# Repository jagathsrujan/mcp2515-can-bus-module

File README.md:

# MCP2515 CAN Bus Module — an agentic PCB design, end to end

A complete hardware design of an MCP2515-based CAN bus module, from the first requirements to a JLCPCB-ready manufacturing package. Nearly all of the engineering work was done by AI agents: **Claude Opus** as lead hardware engineer and reviewer, with **Claude Sonnet** subagents doing the research and the hands-on KiCad work. A human approved each phase before the next one started.

| | |
|---|---|
| **Board** | Rev A, 70 × 50 mm, 2-layer, 1.6 mm FR-4, 1 oz, all SMD on the top side |
| **Function** | Stand-alone CAN 2.0B controller (MCP2515) + ISO 11898-2 transceiver (TCAN1042), SPI to any 3.3 V or 5 V host |
| **Power** | 9 V DC input (7–16 V operating), protected, 5 V buck on board |
| **Design size** | 73 components, 43 nets, 4 schematic sheets |
| **Checks** | ERC 0 · DRC 0 · schematic/PCB parity 0 · 0 unconnected pads |
| **Status** | Phase 8 complete: validated for a prototype order. **Not yet fabricated or bench-tested.** |

---

## 1. What the board does

```
 9V ─J1─[PTC]─[SS34]─[TVS + 100µF]─[ferrite]─[AP63205 5V buck]─┬─ +5V ──► TCAN1042 VCC (bus side)
                                                                └─[3.3V LDO]·· SJ1 (open) ··┐
                                                                                            ▼
 Host ─J2─ VIO (3.0–5.5 V) ─────────────────────────────────────────┬──► MCP2515 VDD
        SCK, MOSI, CS, RST ──► MCP2515 ◄── 16 MHz crystal           └──► TCAN1042 VIO
        MISO, INT ◄─────────── MCP2515
                                 │TXCAN ▲RXCAN
                                 ▼      │
                         TCAN1042 ──[CMC footprint, DNP]──[split 120 Ω, JP1]──[CAN TVS]── J3 / J4
```

The main architecture decision (D-001) is a **host-referenced logic domain**. The MCP2515 and the transceiver's logic pins both run from the host's own `VIO` pin, so the board works with a 3.3 V ESP32/STM32 or a 5 V Arduino without level shifters and without a jumper that could put 5 V into a 3.3 V host. The transceiver's bus side runs from an on-board 5 V rail, so the CAN levels are full ISO 11898-2 whatever the host voltage.

Other features:
- Reverse-polarity, overcurrent (PTC) and transient (TVS) protection on the 9 V input
- ±20 kV ESD protection on CAN_H / CAN_L (PESD2CANFD27V), placed at the connectors
- Split 2 × 60 Ω termination with a 4.7 nF centre tap, both legs switched by jumper JP1
- Two CAN terminals for daisy-chaining, an optional common-mode choke footprint, an optional 3.3 V LDO for testing without a host
- Exact bit timing at 125 k / 250 k / 500 k / 1 Mbit/s from the 16 MHz crystal
- 12 labelled test points, 3 fiducials, 2 × M3 mounting holes

## 2. How the agents worked

### Roles

| Role | Model | Did |
|---|---|---|
| Human | — | Wrote the brief, answered open questions, **approved every phase** before the next started, made sourcing calls (e.g. the MCP2515 part number change) |
| Lead engineer / reviewer | Claude Opus | Requirements, architecture, every design decision and calculation, plans for each phase, and **independent verification** of everything the builders produced |
| Researchers / builders | Claude Sonnet subagents | Datasheet extraction, JLCPCB capability research, schematic capture and PCB layout in KiCad through the KiCad MCP server, manufacturing exports, stock checks |

### Rules that kept it honest

1. **One source of truth.** [`docs/ENGINEERING_SPEC.md`](docs/ENGINEERING_SPEC.md) holds every requirement (R-xx), decision (D-001…D-032), open question (Q-xx) and a change log. Every session read it first, and Sonnet was not allowed to override a decision marked APPROVED.
2. **Phase gates.** Eight phases, each ending with a written report and a human approval. No phase started before the previous one was approved.
3. **Every number is tagged.** `[DS]` datasheet-verified with document and section, `[DS-pending]` quoted from memory and still to be checked, `[CALC]` calculated, `[ASSUME]` assumption, `[TEST]` needs a bench check. Values from memory were not used for final choices until a datasheet confirmed them.
4. **Plan → build → independent review.** Opus wrote the plan, Sonnet built it, then Opus re-checked with its own tools instead of trusting the builder's report: it re-ran ERC/DRC itself, parsed a fresh netlist export with its own parser, compared symbol pin maps with the datasheets, measured distances in the PCB with a pcbnew script, and opened every render.
5. **Margins over minimums.** JLCPCB rules were researched first and every project rule sits above JLC's limits (e.g. 0.15 mm track/space vs 0.10, 0.3 mm vias vs 0.15).

### The eight phases

| Phase | What happened | Output |
|---|---|---|
| 1. Requirements & architecture | Brief turned into requirements; derived requirements proposed (7–16 V input, VIO 3.0–5.5 V, ≤ 100 × 100 mm); block diagram, voltage domains, current budget; JLCPCB capabilities researched and copper-pour strategy set | [Spec §1–§6](docs/ENGINEERING_SPEC.md), [`jlcpcb_capabilities.md`](docs/research/jlcpcb_capabilities.md) |
| 2. Component selection | Candidates scored per function against datasheets, JLC stock and Basic/Extended class. Found that the planned P-MOSFET reverse-polarity stage would be overstressed at the TVS clamp voltage → switched to an SS34 Schottky (D-006r) | [`phase2_component_selection.md`](docs/phase2_component_selection.md), [`research/`](docs/research/) |
| 3. Power supply | LDO vs buck trade: LDOs fail thermally at 16 V / 85 °C → AP63205 buck. Full input protection chain and abs-max check at the 29.2 V clamp | [`phase3_power_supply.md`](docs/phase3_power_supply.md), [`power_budget.xlsx`](docs/power_budget.xlsx) |
| 4. MCP2515 & oscillator | 16 MHz crystal, load caps, drive level, bit-timing register values, reset and SPI conditioning | [`phase4_mcp2515_oscillator.md`](docs/phase4_mcp2515_oscillator.md) |
| 5. CAN physical layer | Transceiver mode pins, termination, TVS, choke option, bus-length limits | [`phase5_can_phy.md`](docs/phase5_can_phy.md) |
| 6. Schematic | Sonnet captured a hierarchical KiCad schematic (Power / Controller / CAN PHY). Opus review: ERC 0, every net checked, one annotation fix (J1B → J5) | [Schematic PDF](docs/schematic/MCP2515_CAN_schematic.pdf), [`phase6_schematic_review.md`](docs/phase6_schematic_review.md) |
| 7. PCB layout | Sonnet placed and routed with its own scripts (placement legaliser, grid A* router, zone/stitching/silk scripts; CAN pair by hand coordinates). Opus review found issues, one correction round fixed them, DRC 0 | [`phase7_pcb_review.md`](docs/phase7_pcb_review.md), [`pcb/layout_report.md`](docs/pcb/layout_report.md) |
| 8. Validation & manufacturing | Gerbers, drill, JLC BOM and CPL, stock check, requirement traceability, risk register, bring-up guide | [`final_design_validation.md`](docs/final/final_design_validation.md), [`manufacturing/`](docs/manufacturing/) |

### What the reviews caught

These are real issues caught by the review step before they reached a board:

- **P-MOSFET overstress (Phase 2):** gate–source and drain–source ratings would be exceeded when the input TVS clamps at 29.2 V, so the reverse-polarity stage was changed to a Schottky diode.
- **Transceiver standby default (Phase 2):** the TCAN1042 STB pin defaults to standby when left open, so a 10 kΩ pull-down was added. Without it the bus would stay silent.
- **No internal reset pull-up (Phase 2):** the MCP2515 has none, so an external 10 kΩ + 10 nF RC was added.
- **INT pin type (Phase 2):** it had been assumed open-drain; the datasheet shows push-pull, so a "don't share INT between modules" warning was documented.
- **ESD diode too far from the connectors (Phase 7):** the first layout put D3 12–18 mm away, with the bus able to branch before it. It was moved between J3/J4 so it is the first thing on the bus.
- **Terminal block drill too small (Phase 7):** the stock footprint had a 1.3 mm drill for a pin that needs 1.4 mm. A project footprint was made with 1.4 mm drill / 2.6 mm pad.
- **Courtyard too close to the edge (Phase 7):** D2 was 2.25 mm from the board edge against a 2.5 mm rule, so it was moved (now ≥ 2.7 mm).
- **Ambiguous "+ centre" silkscreen (Phase 7):** fixed.
- **End-of-life part (Phase 8):** JLC listed the MCP2515 part C12368 as no longer manufactured. It was switched to C153782 (MCP2515T-I/SO, same chip on tape and reel), and ERC/DRC were re-run.

### Tools

- **KiCad 10.0.8**, driven by Sonnet through a KiCad MCP server, plus `kicad-cli` for ERC, DRC, netlist, Gerber, drill, PDF and STEP exports
- Python scripts (pcbnew and s-expression parsing) for placement, routing, measurement and independent netlist checks
- Datasheets from the manufacturers and LCSC, and JLCPCB's own capability pages and KiCad export guide, all cited by URL in the research files
- Claude Code (desktop app) as the agent harness

## 3. Key design numbers

| Item | Value |
|---|---|
| +5V worst-case load | 114 mA (incl. 100 mA bus-short current) vs 150 mA design, buck rated 2 A |
| Hottest part | ≈ 45 mW (buck), so no thermal design needed |
| Input abs-max check | Everything survives the 29.2 V TVS clamp (SS34 40 V, C1 35 V, buck 35 V) |
| Reverse input | 16 V reverse blocked by D1 (40 V rating) |
| Bit timing (CNF1/2/3) | 1M 0x00/0x83/0x01 · 500k 0x00/0xAE/0x01 · 250k 0x01/0xAE/0x01 · 125k 0x03/0xAE/0x01 |
| Max bus length | ≈ 10–15 m at 1 Mbit/s, 52 m at 500k, 140 m at 250k, 315 m at 125k |
| Layout | Crystal 28 mm from the buck inductor; buck hot loop ≈ 4 mm²; decoupling ≤ 2 mm from pins; solid bottom ground; 126+ stitching vias; CAN pair length-matched |
| JLC rules | Track/space 0.15/0.15 mm min, vias 0.3/0.6 mm, copper 0.5 mm from edge, silk ≥ 1 mm |
| Component cost | ≈ $8.50 per board (Sonnet estimate, excl. PCB, assembly and Extended-part fees) |

## 4. Repository map

| What | Where |
|---|---|
| Spec, decisions and change log | [`docs/ENGINEERING_SPEC.md`](docs/ENGINEERING_SPEC.md) |
| Phase reports | `docs/phase2…phase7_*.md`, block netlists `docs/*_netlist.md` |
| Datasheet extracts & JLC research | [`docs/research/`](docs/research/) |
| KiCad project | [`kicad/MCP2515_CAN/`](kicad/MCP2515_CAN/) (with custom footprints in `MCP2515_CAN.pretty/`) |
| Schematic | [PDF](docs/schematic/MCP2515_CAN_schematic.pdf), sheet PNGs, netlist, BOM, ERC report in [`docs/schematic/`](docs/schematic/) |
| PCB | renders, layer images, DRC report, [3D STEP](docs/pcb/MCP2515_CAN.step) in [`docs/pcb/`](docs/pcb/) |
| Manufacturing (JLCPCB) | [Gerber zip](docs/manufacturing/MCP2515_CAN_RevA_gerbers.zip), BOM, CPL, rotation review, stock check in [`docs/manufacturing/`](docs/manufacturing/) |
| Final docs | [validation](docs/final/final_design_validation.md), [BOM](docs/final/BOM_final.csv), [connector pinouts](docs/final/connector_pinouts.md), [design notes](docs/final/design_notes.md), [testing & commissioning](docs/final/testing_commissioning.md) |

| Top copper + silk | Bottom copper |
|---|---|
|  |  |

## 5. What's still open

The design is validated on paper, not on a bench. The full risk register (K-01…K-17) is in [`final_design_validation.md` §9](docs/final/final_design_validation.md). The main items:

- **Before paying for the order:** check every part's rotation and polarity in JLC's placement preview, especially D1, D2, LED D4 and crystal Y1, which had no rotation-database rule. A reversed D2 would short the input. Also re-check stock and Extended-part fees.
- **On the first boards:** measure crystal drive level at 5 V VIO (calculated 227 µW vs 200 µW max; fit R4 ≈ 1 kΩ if needed), crystal frequency via CLKOUT, and +5V ripple at idle and under 1 Mbit/s traffic. Also check the fit of the three footprints made from datasheet drawings (barrel jack, terminal blocks, choke).
- **Not tested:** EMC emissions and IEC 61000-4-2 ESD.
- **Usage limits:** 7–16 V supplies only, centre-positive jack; ≤ 10 m bus at 1 Mbit/s; not for 24 V vehicle buses (the 27 V TVS standoff would conduct at charge voltage); one INT line per module.

The bring-up order and expected readings are in [`testing_commissioning.md`](docs/final/testing_commissioning.md).

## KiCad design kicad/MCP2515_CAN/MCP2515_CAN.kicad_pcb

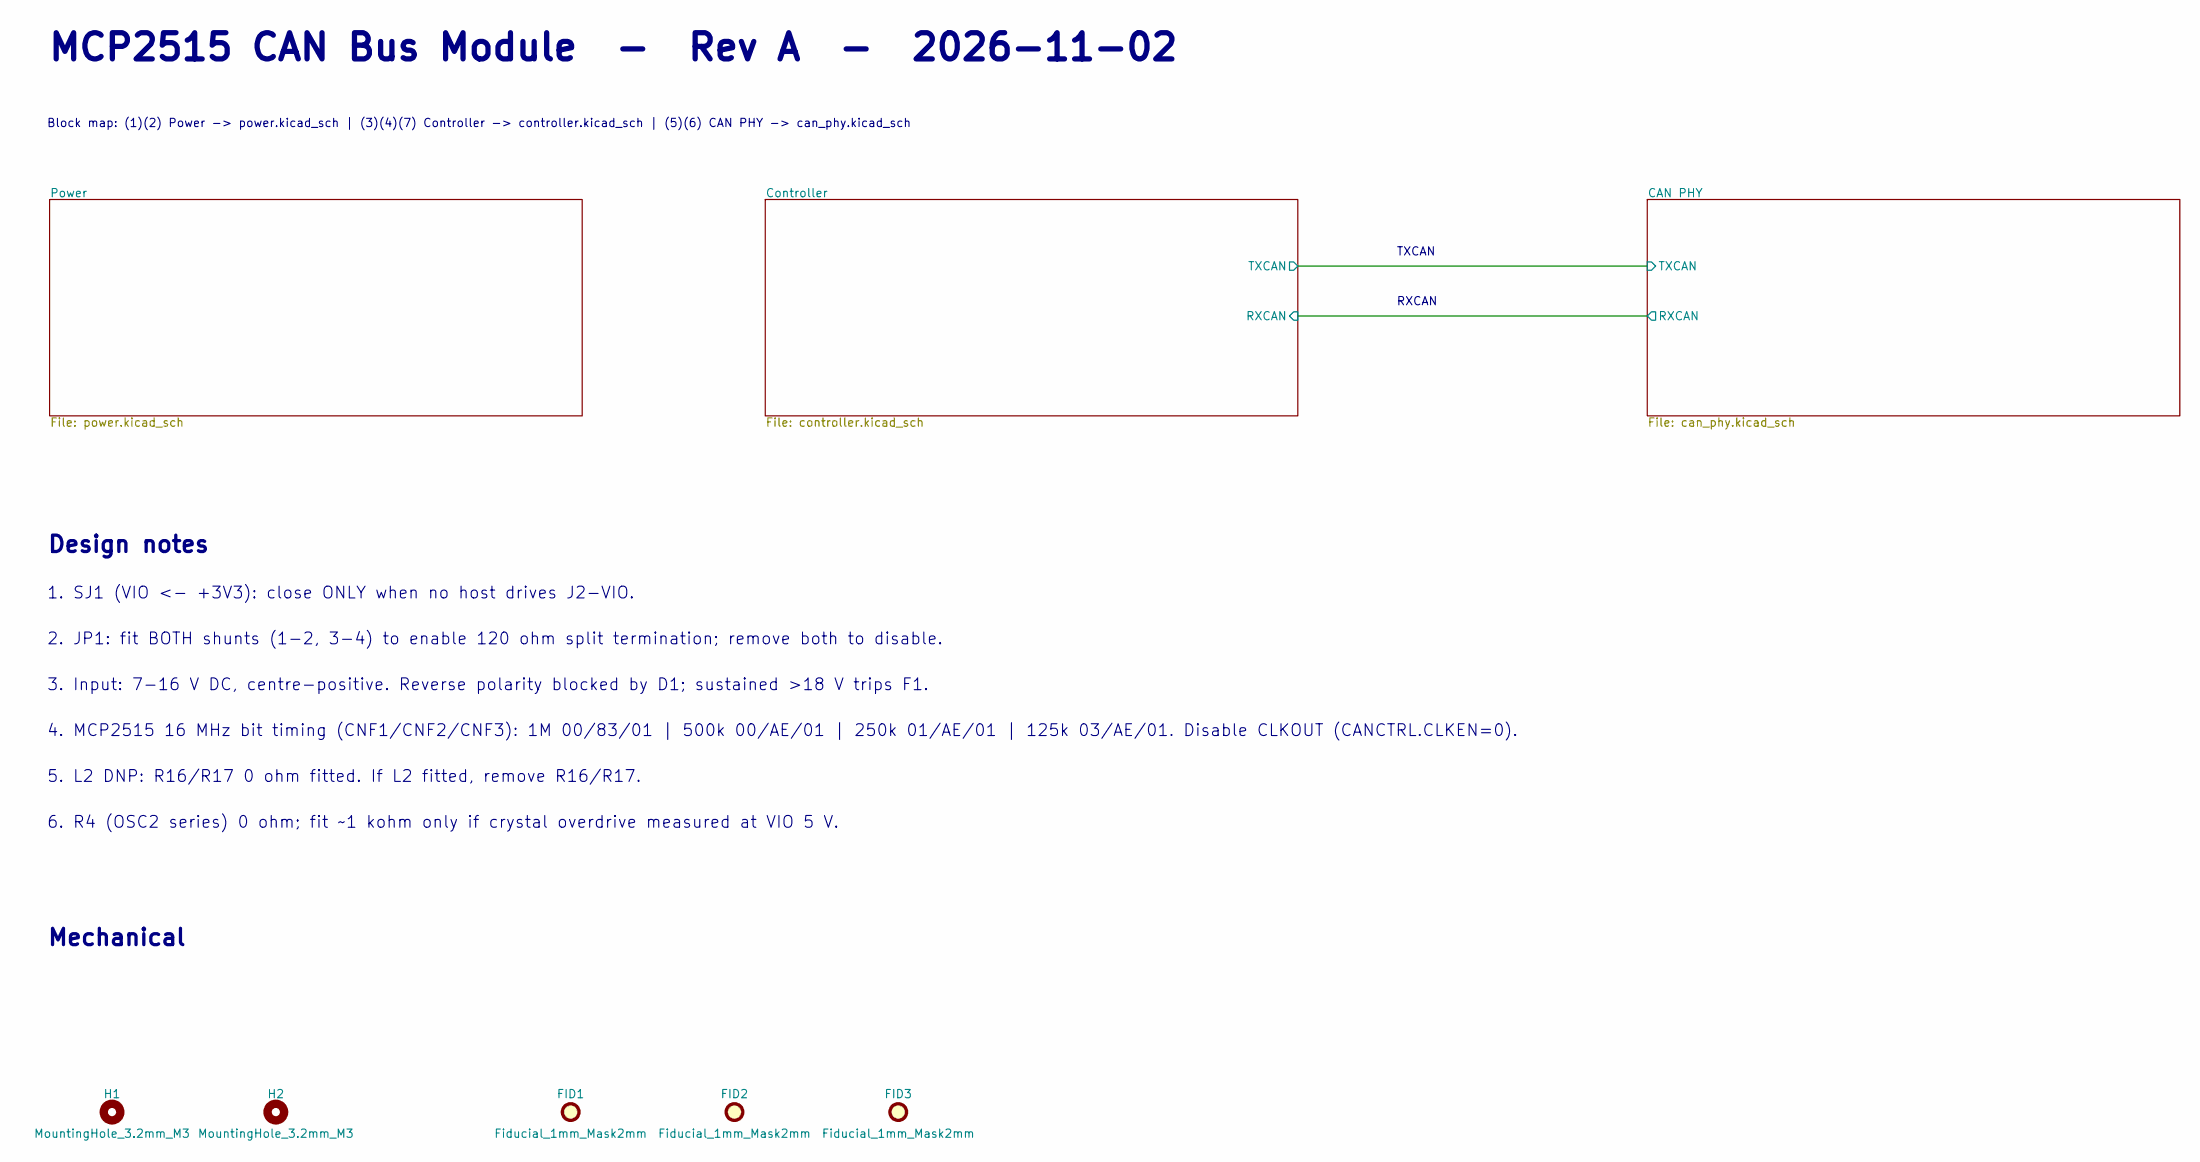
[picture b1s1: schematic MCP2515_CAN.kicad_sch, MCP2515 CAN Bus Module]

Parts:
FID1, FID2, FID3: Fiducial_1mm_Mask2mm
H1, H2: MountingHole_3.2mm_M3

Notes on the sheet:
TXCAN
RXCAN
MCP2515 CAN Bus Module - Rev A - 2026-11-02
Block map: (1)(2) Power -> power.kicad_sch | (3)(4)(7) Controller -> controller.kicad_sch | (5)(6) CAN PHY -> can_phy.kicad_sch
Design notes
1. SJ1 (VIO <- +3V3): close ONLY when no host drives J2-VIO.
2. JP1: fit BOTH shunts (1-2, 3-4) to enable 120 ohm split termination; remove both to disable.
3. Input: 7-16 V DC, centre-positive. Reverse polarity blocked by D1; sustained >18 V trips F1.
4. MCP2515 16 MHz bit timing (CNF1/CNF2/CNF3): 1M 00/83/01 | 500k 00/AE/01 | 250k 01/AE/01 | 125k 03/AE/01. Disable CLKOUT (CANCTRL.CLKEN=0).
5. L2 DNP: R16/R17 0 ohm fitted. If L2 fitted, remove R16/R17.
6. R4 (OSC2 series) 0 ohm; fit ~1 kohm only if crystal overdrive measured at VIO 5 V.
Mechanical

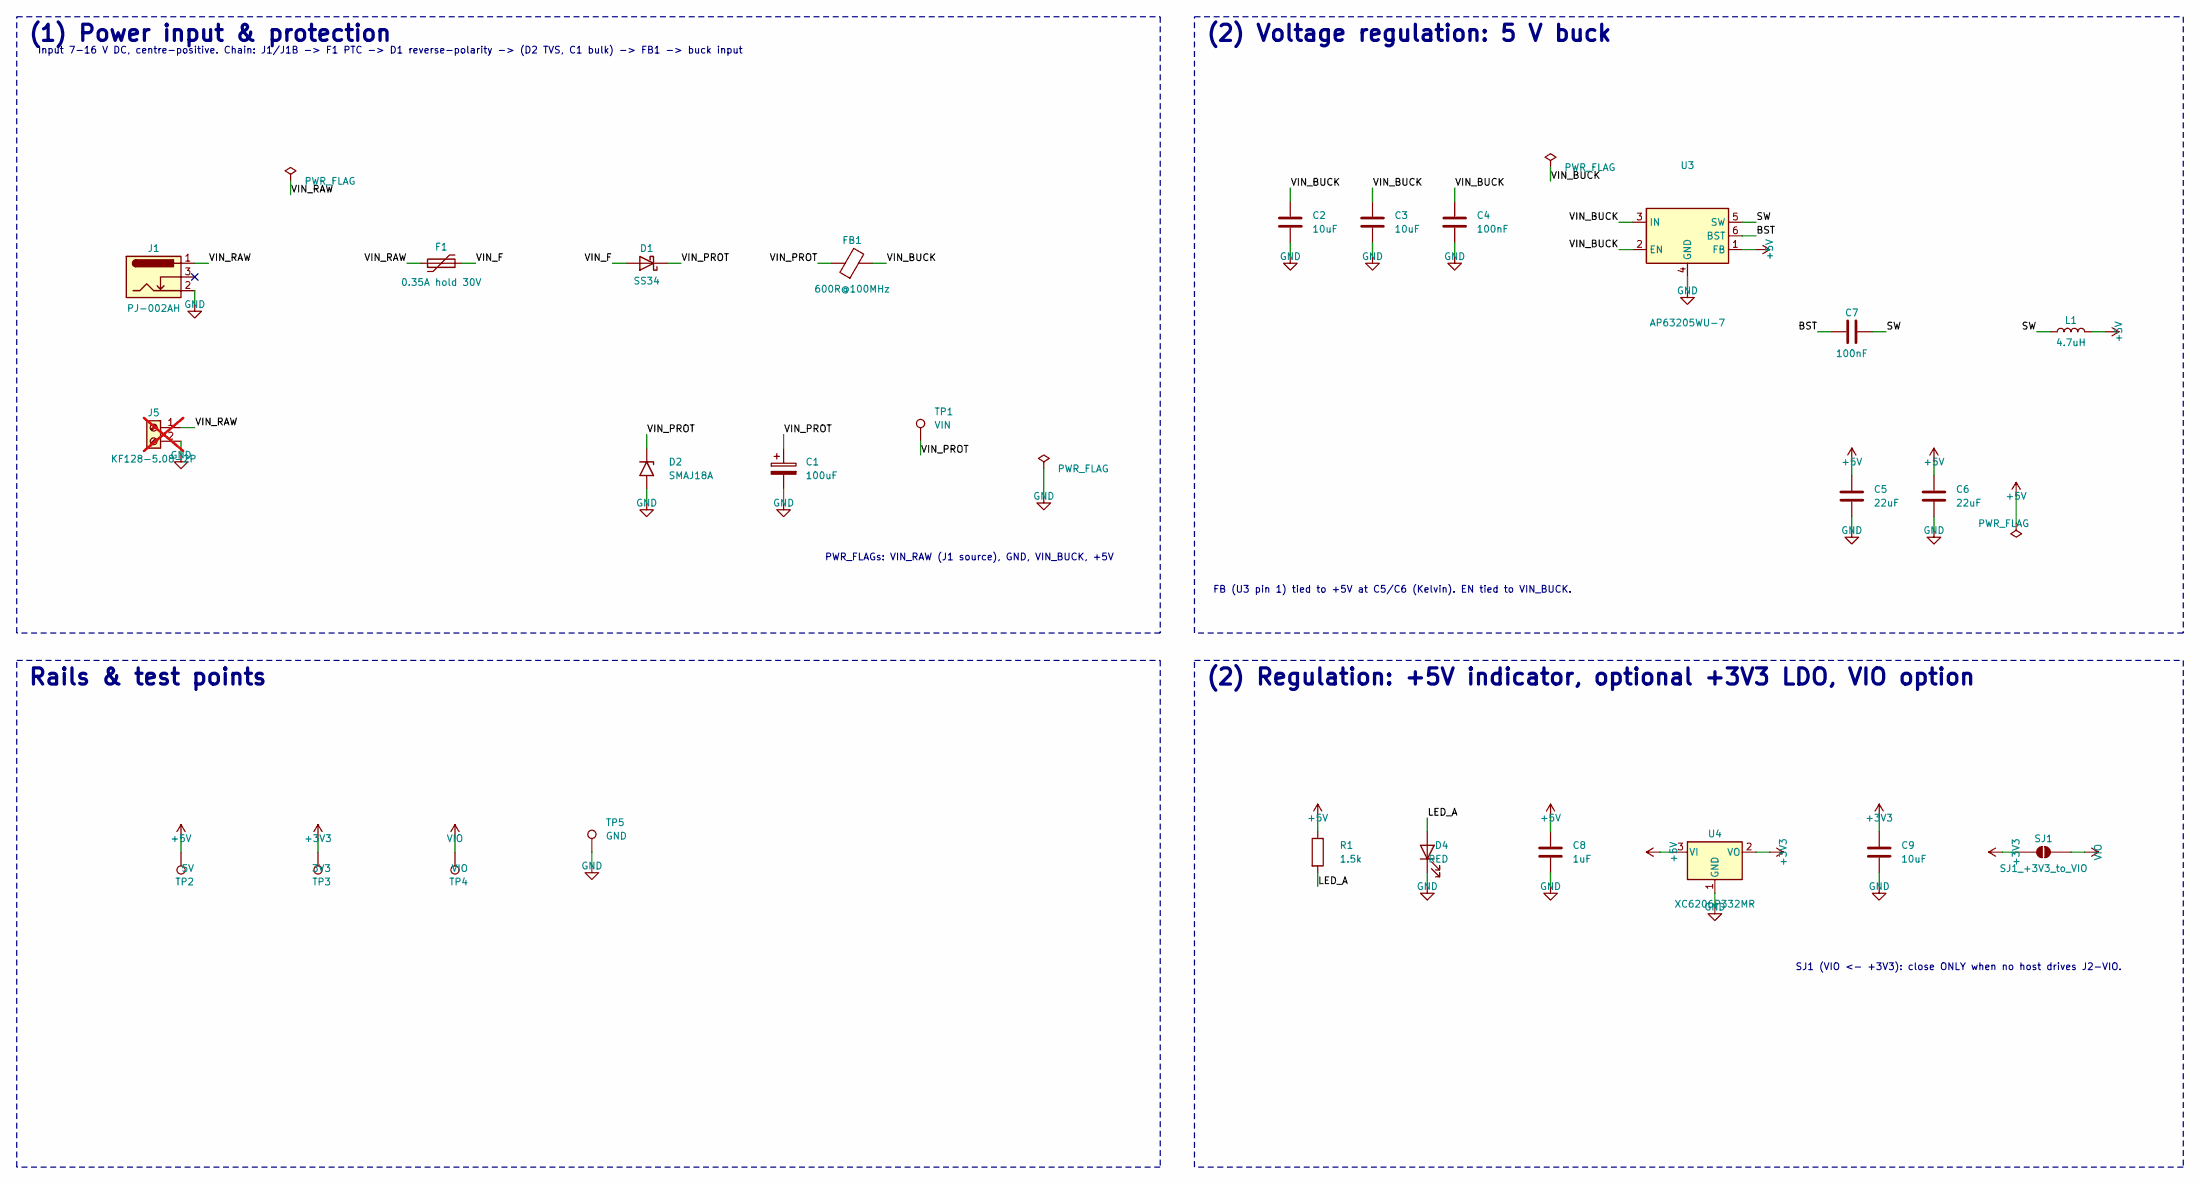
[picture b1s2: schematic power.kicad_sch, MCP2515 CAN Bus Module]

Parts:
C1: 100uF; CP_Elec_6.3x7.7; MPN FZ100UF35V90RV0064; LCSC C2992596
C2, C3: 10uF; C_1206_3216Metric; MPN CL31A106KBHNNNE; LCSC C13585
C4, C7: 100nF; C_0603_1608Metric; MPN CC0603KRX7R9BB104; LCSC C14663
C5, C6: 22uF; C_1206_3216Metric; MPN CL31A226KAHNNNE; LCSC C12891
C8: 1uF; C_0603_1608Metric; MPN CL10A105KB8NNNC; LCSC C15849
C9: 10uF; C_0805_2012Metric; MPN CL21A106KAYNNNE; LCSC C15850
D1: SS34; D_SMA; MPN SS34; LCSC C8678
D2: SMAJ18A; D_SMA; MPN SMAJ18A; LCSC C148219
D4: RED; LED_0603_1608Metric; MPN KT-0603R; LCSC C2286
F1: 0.35A hold 30V; Fuse_1206_3216Metric; MPN 0ZCJ0035AF2E; LCSC C6378052
FB1: 600R@100MHz; L_0805_2012Metric; MPN GZ2012D601TF; LCSC C1017
J1: PJ-002AH; BarrelJack_CUI_PJ-002AH; MPN PJ-002AH; LCSC C2961147
J5: KF128-5.08-2P; KF128-5.08-2P_Horizontal; MPN KF128-5.08-2P; LCSC C474952; not fitted
L1: 4.7uH; L_Sunlord_SWPA4020S; MPN SWPA4020S4R7MT; LCSC C48427
R1: 1.5k; R_0603_1608Metric; MPN 0603WAF1501T5E; LCSC C22843
SJ1: SJ1_+3V3_to_VIO; SolderJumper-2_P1.3mm_Open_RoundedPad1.0x1.5mm
TP1: VIN; TestPoint_Pad_D1.5mm
TP2: 5V; TestPoint_Pad_D1.5mm
TP3: 3V3; TestPoint_Pad_D1.5mm
TP4: VIO; TestPoint_Pad_D1.5mm
TP5: GND; TestPoint_Pad_D1.5mm
U3: AP63205WU-7; TSOT-23-6; MPN AP63205WU-7; LCSC C2071056
U4: XC6206P332MR; SOT-23-3; MPN XC6206P332MR; LCSC C5446

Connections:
+3V3: C9.1, SJ1.1 (A), TP3.1, U4.2 (VO)
+5V: C5.1, C6.1, C8.1, L1.2, R1.1, TP2.1, U3.1 (FB), U4.3 (VI); also elsewhere on the board
/Power/BST: C7.1, U3.6 (BST)
/Power/LED_A: D4.2 (A), R1.2
/Power/SW: C7.2, L1.1, U3.5 (SW)
/Power/VIN_BUCK: C2.1, C3.1, C4.1, FB1.2, U3.2 (EN), U3.3 (IN)
/Power/VIN_F: D1.2 (A), F1.2
/Power/VIN_PROT: C1.1, D1.1 (K), D2.1 (A1), FB1.1, TP1.1
/Power/VIN_RAW: F1.1, J1.1, J5.1
GND: C1.2, C2.2, C3.2, C4.2, C5.2, C6.2, C8.2, C9.2, D2.2 (A2), D4.1 (K), J1.2, J5.2, TP5.1, U3.4 (GND), U4.1 (GND); also elsewhere on the board
VIO: SJ1.2 (B), TP4.1; also elsewhere on the board

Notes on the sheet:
(1) Power input & protection
Input 7-16 V DC, centre-positive. Chain: J1/J1B -> F1 PTC -> D1 reverse-polarity -> (D2 TVS, C1 bulk) -> FB1 -> buck input
PWR_FLAGs: VIN_RAW (J1 source), GND, VIN_BUCK, +5V
(2) Voltage regulation: 5 V buck
FB (U3 pin 1) tied to +5V at C5/C6 (Kelvin). EN tied to VIN_BUCK.
Rails & test points
(2) Regulation: +5V indicator, optional +3V3 LDO, VIO option
SJ1 (VIO <- +3V3): close ONLY when no host drives J2-VIO.

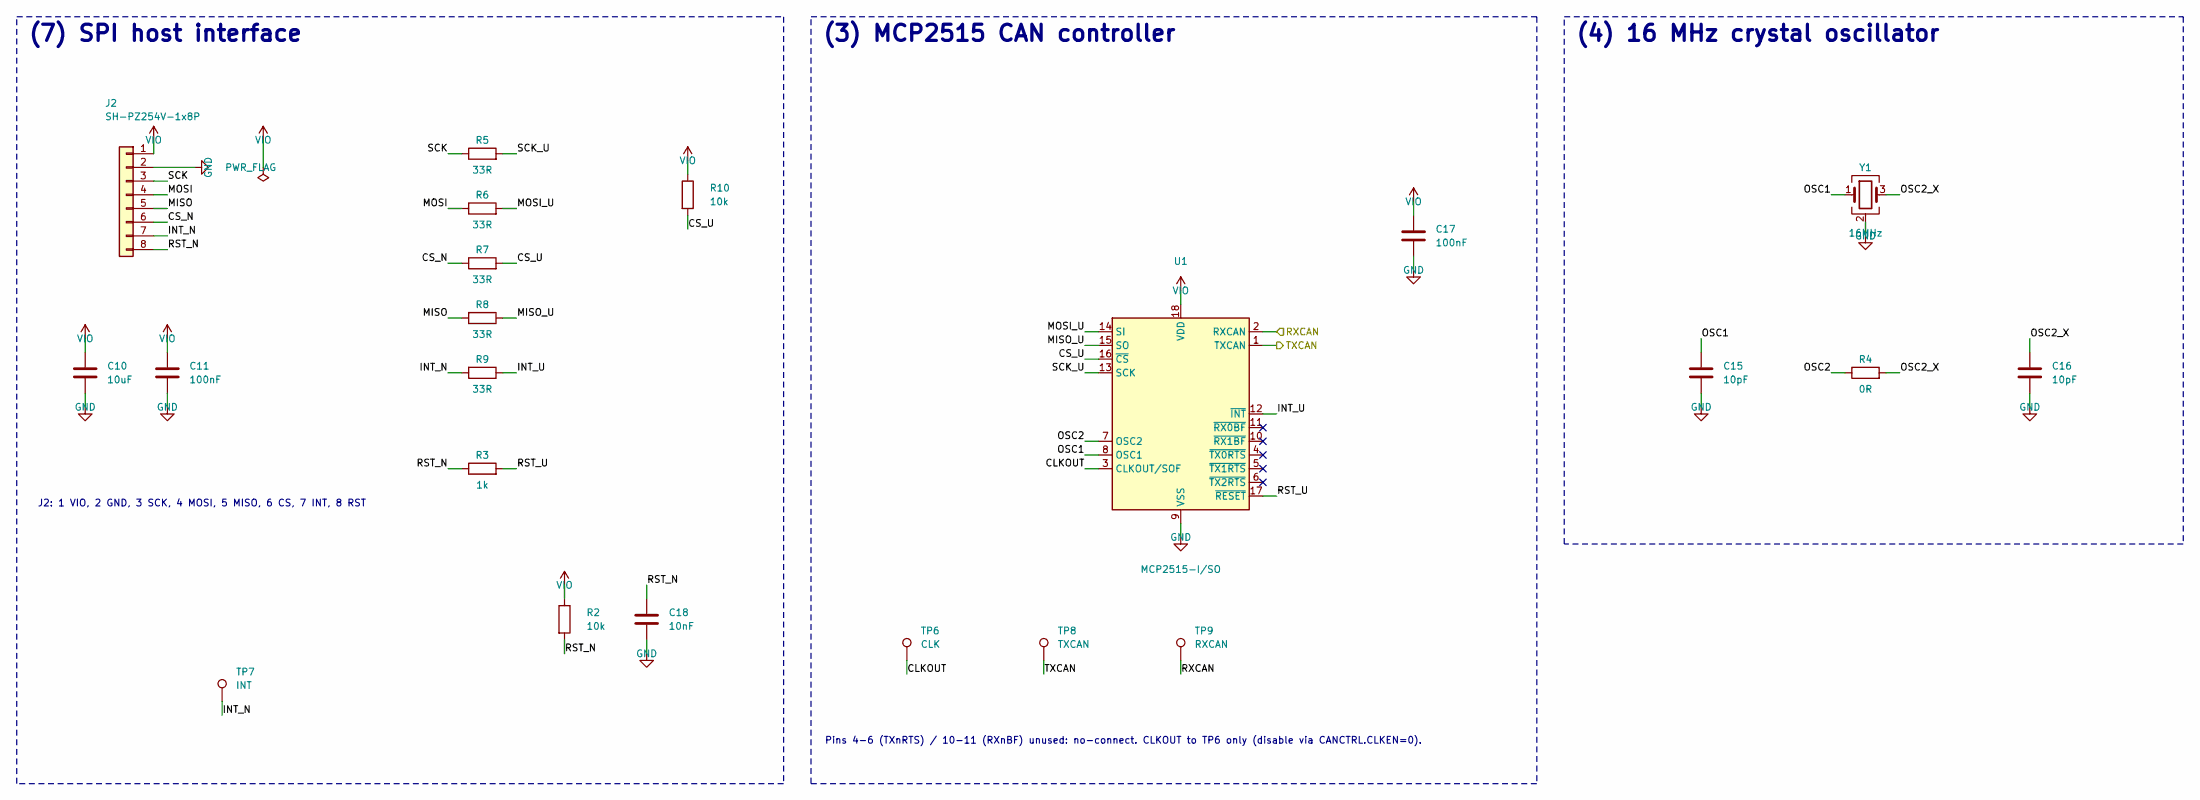
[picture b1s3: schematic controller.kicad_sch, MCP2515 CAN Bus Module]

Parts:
C10: 10uF; C_0805_2012Metric; MPN CL21A106KAYNNNE; LCSC C15850
C11, C17: 100nF; C_0603_1608Metric; MPN CC0603KRX7R9BB104; LCSC C14663
C15, C16: 10pF; C_0603_1608Metric; MPN CL10C100JB8NNNC; LCSC C1634
C18: 10nF; C_0603_1608Metric; MPN 0603B103K500NT; LCSC C57112
J2: SH-PZ254V-1x8P; PinHeader_1x08_P2.54mm_Vertical; MPN SH-PZ254V-1x8P; LCSC C55629815
R2, R10: 10k; R_0603_1608Metric; MPN 0603WAF1002T5E; LCSC C25804
R3: 1k; R_0603_1608Metric; MPN 0603WAF1001T5E; LCSC C21190
R4: 0R; R_0603_1608Metric; MPN 0603WAF0000T5E; LCSC C21189
R5, R6, R7, R8, R9: 33R; R_0603_1608Metric; MPN 0603WAF330JT5E; LCSC C23140
TP6: CLK; TestPoint_Pad_D1.5mm
TP7: INT; TestPoint_Pad_D1.5mm
TP8: TXCAN; TestPoint_Pad_D1.5mm
TP9: RXCAN; TestPoint_Pad_D1.5mm
U1: MCP2515-I/SO; SOIC-18W_7.5x11.6mm_P1.27mm; MPN MCP2515T-I/SO; LCSC C153782
Y1: 16MHz; Crystal_SMD_3225-4Pin_3.2x2.5mm; MPN X322516MLB4SI; LCSC C13738

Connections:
/Controller/CLKOUT: TP6.1, U1.3 (CLKOUT/SOF)
/Controller/CS_N: J2.6, R7.1
/Controller/CS_U: R7.2, R10.2, U1.16 (~CS)
/Controller/INT_N: J2.7, R9.2, TP7.1
/Controller/INT_U: R9.1, U1.12 (~INT)
/Controller/MISO: J2.5, R8.2
/Controller/MISO_U: R8.1, U1.15 (SO)
/Controller/MOSI: J2.4, R6.1
/Controller/MOSI_U: R6.2, U1.14 (SI)
/Controller/OSC1: C15.1, U1.8 (OSC1), Y1.1
/Controller/OSC2: R4.1, U1.7 (OSC2)
/Controller/OSC2_X: C16.1, R4.2, Y1.3
/Controller/RST_N: C18.1, J2.8, R2.2, R3.1
/Controller/RST_U: R3.2, U1.17 (~RESET)
/Controller/RXCAN: TP9.1, U1.2 (RXCAN); also elsewhere on the board
/Controller/SCK: J2.3, R5.1
/Controller/SCK_U: R5.2, U1.13 (SCK)
/Controller/TXCAN: TP8.1, U1.1 (TXCAN); also elsewhere on the board
GND: C10.2, C11.2, C15.2, C16.2, C17.2, C18.2, J2.2, U1.9 (VSS), Y1.2 (G), Y1.4 (G); also elsewhere on the board
VIO: C10.1, C11.1, C17.1, J2.1, R2.1, R10.1, U1.18 (VDD); also elsewhere on the board

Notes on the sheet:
(7) SPI host interface
J2: 1 VIO, 2 GND, 3 SCK, 4 MOSI, 5 MISO, 6 CS, 7 INT, 8 RST
(3) MCP2515 CAN controller
Pins 4-6 (TXnRTS) / 10-11 (RXnBF) unused: no-connect. CLKOUT to TP6 only (disable via CANCTRL.CLKEN=0).
(4) 16 MHz crystal oscillator

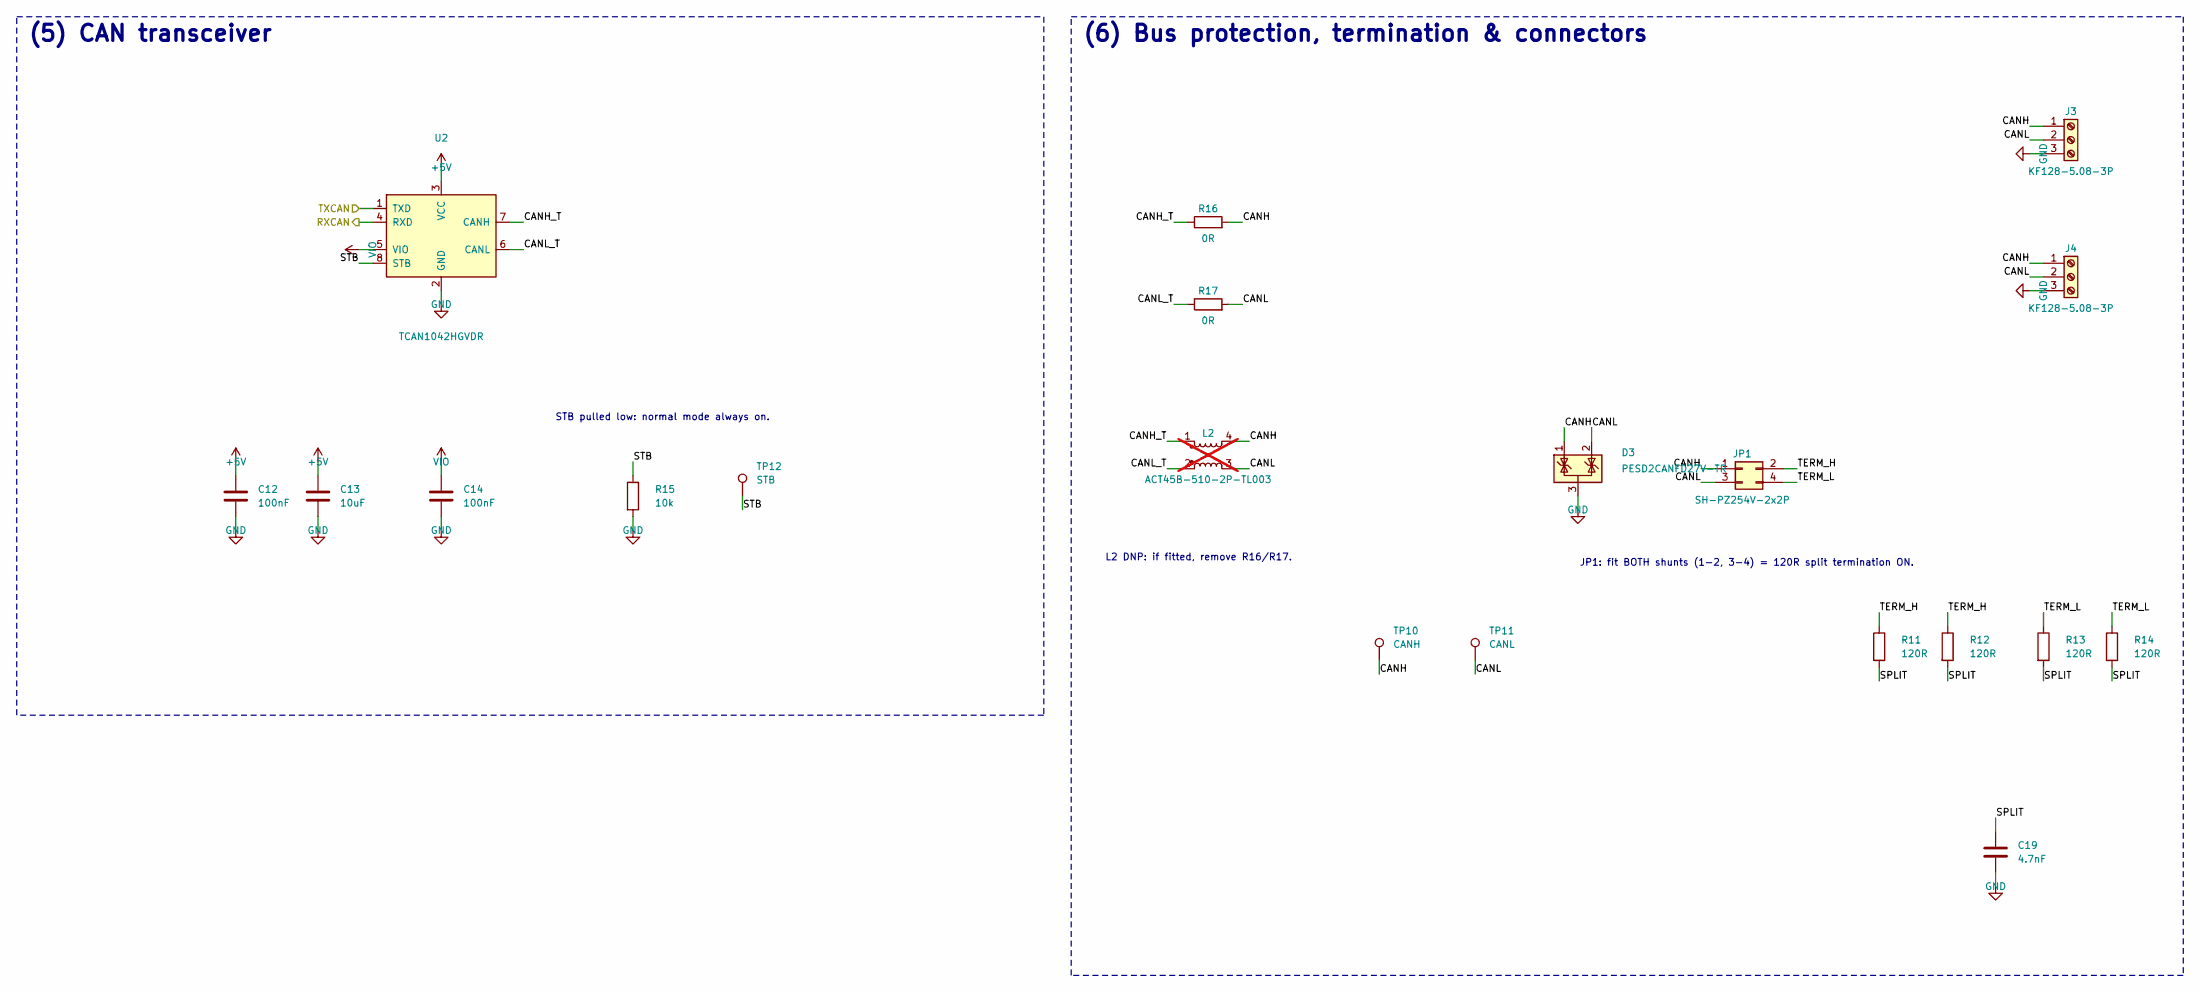
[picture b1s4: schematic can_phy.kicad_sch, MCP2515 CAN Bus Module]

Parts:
C12, C14: 100nF; C_0603_1608Metric; MPN CC0603KRX7R9BB104; LCSC C14663
C13: 10uF; C_0805_2012Metric; MPN CL21A106KAYNNNE; LCSC C15850
C19: 4.7nF; C_0603_1608Metric; MPN 0603B472K500NT; LCSC C53987
D3: PESD2CANFD27V-TR; SOT-23; MPN PESD2CANFD27V-TR; LCSC C552488
J3, J4: KF128-5.08-3P; KF128-5.08-3P_Horizontal; MPN KF128-5.08-3P; LCSC C474953
JP1: SH-PZ254V-2x2P; PinHeader_2x02_P2.54mm_Vertical; MPN SH-PZ254V-2x2P; LCSC C55629823
L2: ACT45B-510-2P-TL003; L_CommonModeChoke_TDK_ACT45B; MPN ACT45B-510-2P-TL003; LCSC C76584; not fitted
R11, R12, R13, R14: 120R; R_0603_1608Metric; MPN 0603WAF1200T5E; LCSC C22787
R15: 10k; R_0603_1608Metric; MPN 0603WAF1002T5E; LCSC C25804
R16, R17: 0R; R_0603_1608Metric; MPN 0603WAF0000T5E; LCSC C21189
TP10: CANH; TestPoint_Pad_D1.5mm
TP11: CANL; TestPoint_Pad_D1.5mm
TP12: STB; TestPoint_Pad_D1.5mm
U2: TCAN1042HGVDR; SOIC-8_3.9x4.9mm_P1.27mm; MPN TCAN1042HGVDR; LCSC C124014

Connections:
+5V: C12.1, C13.1, U2.3 (VCC); also elsewhere on the board
/CAN PHY/CANH: D3.1 (K), J3.1, J4.1, JP1.1, L2.4, R16.2, TP10.1
/CAN PHY/CANH_T: L2.1, R16.1, U2.7 (CANH)
/CAN PHY/CANL: D3.2 (K), J3.2, J4.2, JP1.3, L2.3, R17.2, TP11.1
/CAN PHY/CANL_T: L2.2, R17.1, U2.6 (CANL)
/CAN PHY/SPLIT: C19.1, R11.2, R12.2, R13.2, R14.2
/CAN PHY/STB: R15.1, TP12.1, U2.8 (STB)
/CAN PHY/TERM_H: JP1.2, R11.1, R12.1
/CAN PHY/TERM_L: JP1.4, R13.1, R14.1
/Controller/RXCAN: U2.4 (RXD); also elsewhere on the board
/Controller/TXCAN: U2.1 (TXD); also elsewhere on the board
GND: C12.2, C13.2, C14.2, C19.2, D3.3 (A), J3.3, J4.3, R15.2, U2.2 (GND); also elsewhere on the board
VIO: C14.1, U2.5 (VIO); also elsewhere on the board

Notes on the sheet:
(5) CAN transceiver
STB pulled low: normal mode always on.
(6) Bus protection, termination & connectors
L2 DNP: if fitted, remove R16/R17.
JP1: fit BOTH shunts (1-2, 3-4) = 120R split termination ON.

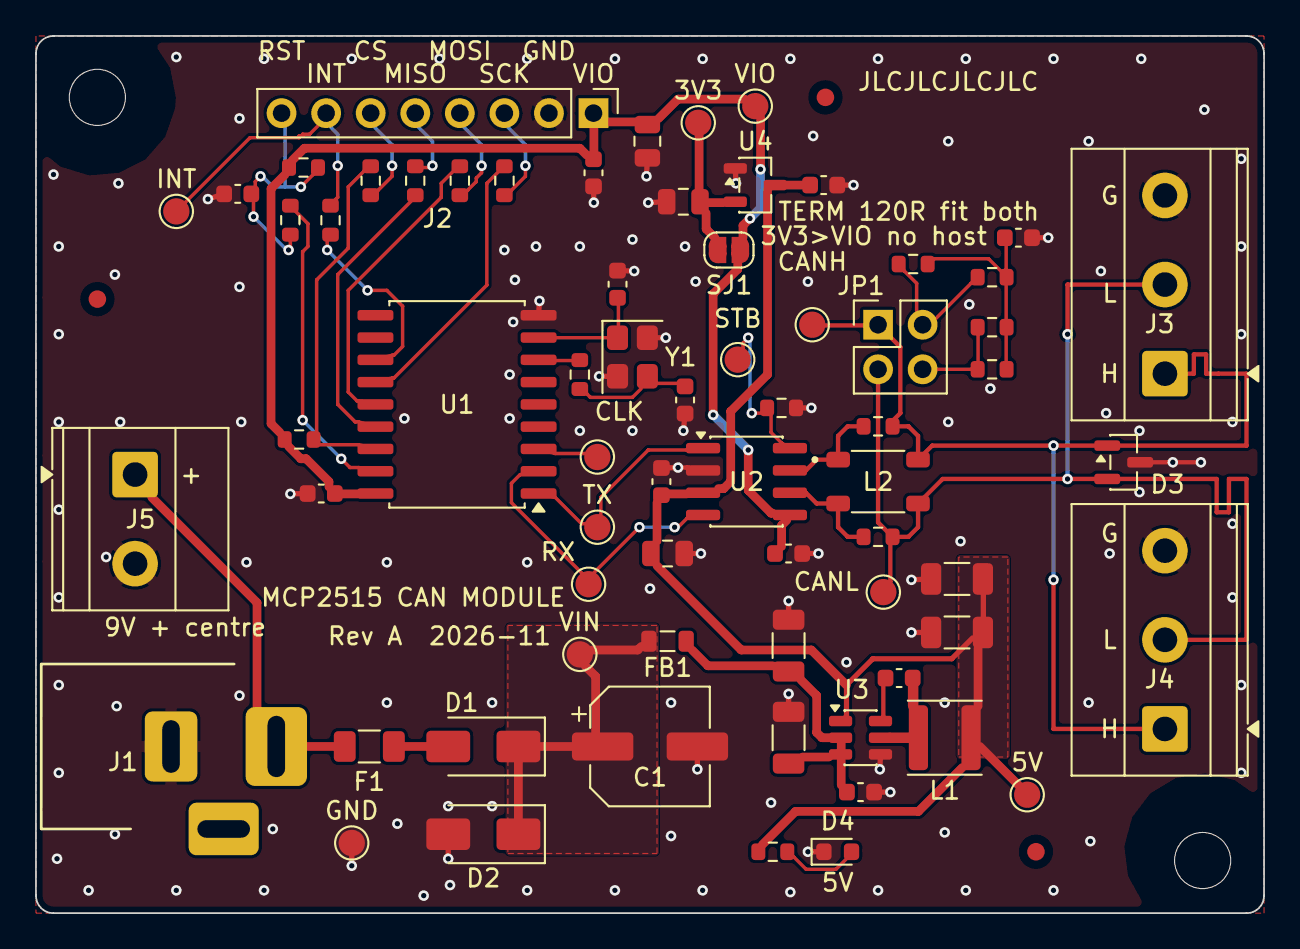
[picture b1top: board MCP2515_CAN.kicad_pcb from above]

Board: 2 copper layers, 70.0 x 50.0 mm, 73 parts (0 on the bottom side), 37 nets.
